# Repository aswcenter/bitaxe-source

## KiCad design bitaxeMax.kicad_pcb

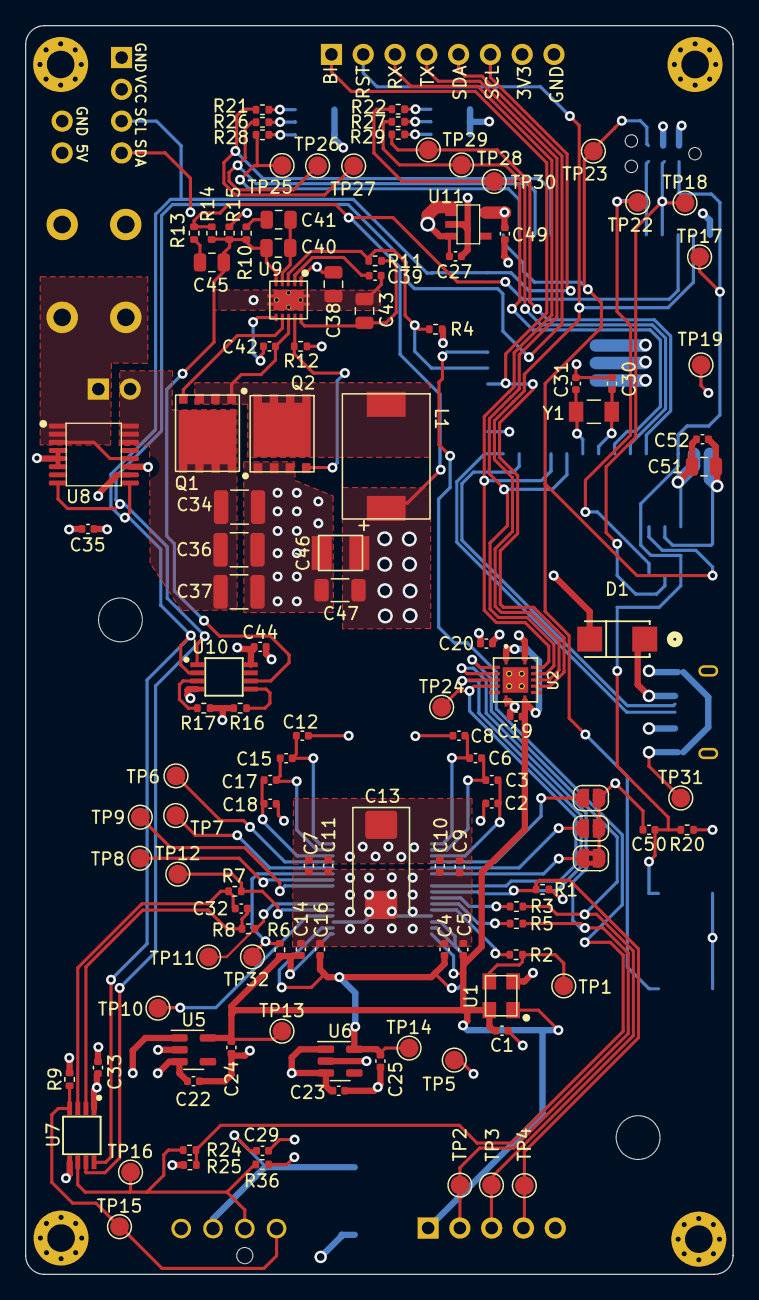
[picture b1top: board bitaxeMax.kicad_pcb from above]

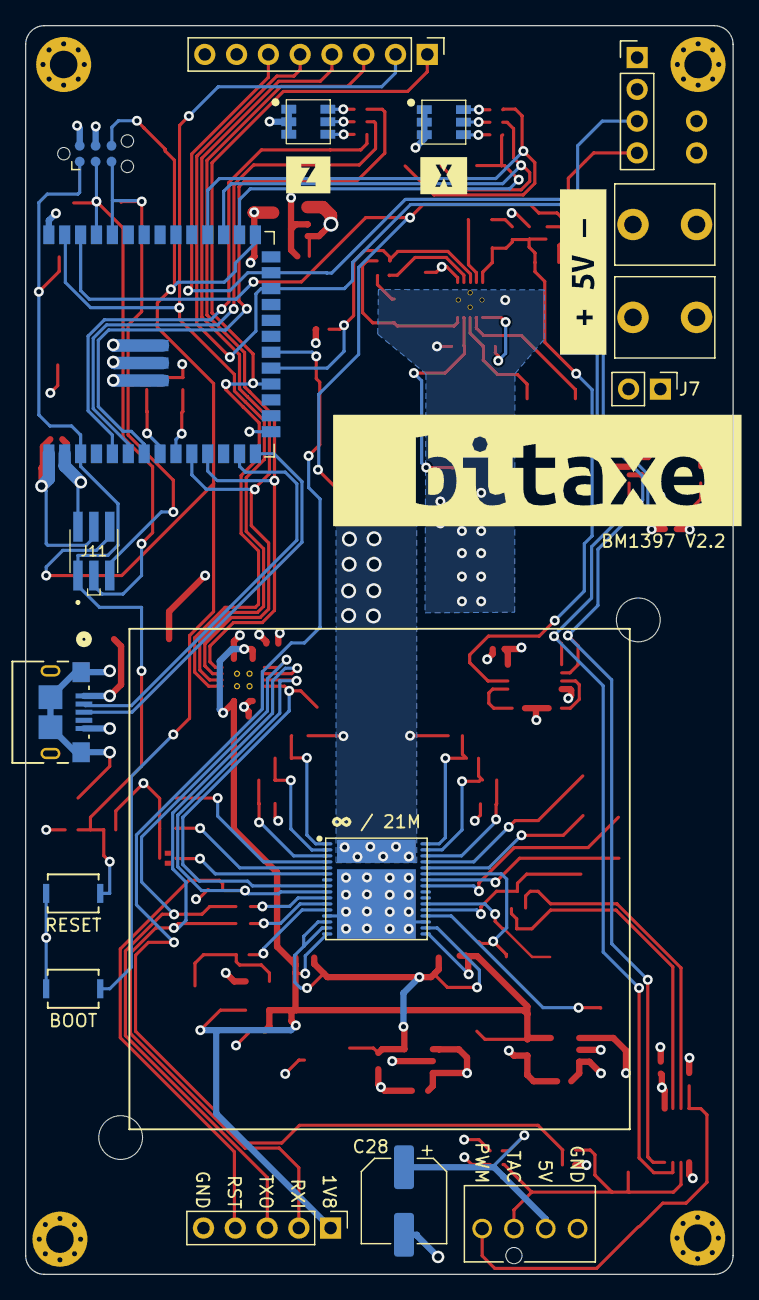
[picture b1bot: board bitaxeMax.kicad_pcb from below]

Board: 4 copper layers, 56.5 x 99.8 mm, 149 parts (21 on the bottom side), 77 nets.

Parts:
C1, C7, C9, C19, C20, C22, C23, C29, C33, C42, C52: 0.1uF; C_0402_1005Metric
C2, C3, C4, C5, C6, C8, C10, C11, C12, C14, C15, C16, C17, C18, C24, C25, C27, C35, C44, C49, C50: 1uF; C_0402_1005Metric
C13: 330uF; CP_EIA-7343-31_Kemet-D_Pad2.25x2.55mm_HandSolder
C28: 220uF; CP_Elec_6.3x7.7
C30, C31: 6.8pF; C_0402_1005Metric
C32: 470pF; C_0402_1005Metric
C34, C36, C37: 47uF; C_1210_3225Metric
C38: 1uF; C_0805_2012Metric
C39: 3.3nF; C_0402_1005Metric
C40: 180pF; C_0805_2012Metric
C41: 1.5nF; C_0805_2012Metric
C43, C51: 10uF; C_0805_2012Metric
C45: 470pF; C_0805_2012Metric
C46: 220uF; CAP_2R5TPE220MAFB
C47: 100uF; C_1206_3216Metric
D1: SS310; SMA_L4.3-W2.6-LS5.2-RD
H1, H2, H3, H4: AlignmentHole; MountingHole_2.2mm_M2_Pad_Via
H5, H6: MountingHole; MountingHole_3.5mm
IC1: BM1397_mode1; BM1397
J1, J2: Conn_01x01; 63862-1
J3: Conn_01x05; PinHeader_1x05_P2.54mm_Vertical
J4: Conn_01x04; 470531000
J5: TC2030-IDC; Tag-Connect_TC2030-IDC-NL_2x03_P1.27mm_Vertical
J6: Conn_01x08; PinHeader_1x08_P2.54mm_Vertical
J7: Conn_01x02; PinHeader_1x02_P2.54mm_Vertical
J9: Conn_01x04; PinHeader_1x04_P2.54mm_Vertical
J11: 20021121-00006C1LF; 2002112100006C1LF
JP1, JP2: SolderJumper_2_Open; SolderJumper-2_P1.3mm_Open_RoundedPad1.0x1.5mm
JP3: SolderJumper_2_Bridged; SolderJumper-2_P1.3mm_Bridged2Bar_RoundedPad1.0x1.5mm
L1: 150nH; FP1005R1-R15-R
Q1, Q2: CSD17311Q5
R1: 1k; R_0402_1005Metric
R2, R3, R5: 0; R_0402_1005Metric
R4, R6, R9, R20, R24, R36: 10k; R_0402_1005Metric
R7, R8, R26, R27: 100; R_0402_1005Metric
R10: 3.83k; R_0402_1005Metric
R11: 100k; R_0402_1005Metric
R12: 4.12k; R_0402_1005Metric
R13: 1.33k; R_0402_1005Metric
R14: 4.99k; R_0402_1005Metric
R15: 3.32k; R_0402_1005Metric
R16: 80k; R_0402_1005Metric
R17: DNP; R_0402_1005Metric
R21, R22: 60.4; R_0402_1005Metric
R25: 19.1k; R_0402_1005Metric
R28, R29: 261; R_0402_1005Metric
SW1, SW2: GT-TC029B-H025-L1N; SW_CS1213AGF260_CRS
TP1, TP2, TP3, TP4, TP5, TP6, TP7, TP8, TP9, TP10, TP11, TP12, TP13, TP14, TP15, TP16, TP17, TP18, TP19, TP22, TP23, TP24, TP25, TP26, TP27, TP28, TP29, TP30, TP31, TP32: TestPoint; TestPoint_Pad_D1.5mm
U1: 25MHz; O 25,0-JO32-B-1V3-1-T1-LF
U2: TXB0104RGYR; TXB0104
U4, U13: CLX6E-FKC; CLX6E-FKC-CH1M1D1BB7C3D3
U5: MCP1824T-1802E; SOT-23-5
U6: MCP1824T-0802E; SOT-23-5
U7: EMC2101; TSSOP-8_3x3mm_P0.65mm
U8: INA260; TSSOP-16_4.4x5mm_P0.65mm
U9: TPS40305
U10: DS4432U+; TSSOP-8_3x3mm_P0.65mm
U11: RT9080-33GJ5
U12: ESP32-S3-WROOM-1
USB1: 10118193-0001LF; USB_10118193-0001LF_AMP
Y1: 32.768kHz; SC32S-7PF20PPM
kibuzzard-63D74789: G***; kibuzzard-63D74789
kibuzzard-6387EEBE: G***; kibuzzard-6387EEBE
kibuzzard-6387EECB: G***; kibuzzard-6387EECB
kibuzzard-6392B1E5: G***; kibuzzard-6392B1E5

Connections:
/3V3: C20.1, C33.1, C35.1, C44.1, C49.1, C51.1, C52.1, J5.2, J6.7, J9.2, J11.2, R4.1, R9.2, R20.1, R36.2, TP19.1, U2.14 (VCCB), U7.1 (VDD), U8.10 (VS), U10.8 (VCC), U11.5 (VOUT), U12.2 (3V3), U12.15 (GPIO3/TOUCH3/ADC1_CH2*)
/5V: C22.1, C23.1, C27.1, C28.1, C29.1, C34.1, C36.1, C37.1, C38.1, D1.1, J4.2, J7.2, Q1.5 (D), U5.1 (VIN), U5.3 (EN), U6.1 (VIN), U6.3 (EN), U8.14 (IN-), U8.15 (IN-), U8.16 (IN-), U9.1 (VDD), U11.1 (VIN), U11.3 (EN)
/BI: J6.1, U2.10 (B4), U12.18 (GPIO10/TOUCH10/ADC1_CH9/FSPICS0/FSPIIO4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)
/BM1397/0V8: C4.1, C16.1, C25.1, IC1.14 (PLL_VDD), IC1.15 (VDDIO_08_0), IC1.18 (VDDIO_08_1), TP14.1, U6.5 (VOUT)
/BM1397/1V8: C1.2, C5.1, C14.1, C19.1, C24.1, IC1.16 (VDDIO_18_0), IC1.17 (VDDIO_18_1), J3.1, R6.2, TP13.1, U1.1 (EN), U1.4 (VIN), U2.1 (VCCA), U2.8 (OE), U5.5 (VOUT)
/BM1397/BM_BI: IC1.8 (BI), TP24.1, U2.5 (A4)
/BM1397/BM_CLKI: IC1.12 (CLKI), R2.2
/BM1397/CI: J3.2, R5.1, TP2.1, U2.3 (A2)
/BM1397/RO: J3.3, R3.1, TP3.1, U2.2 (A1)
/BM1397/RST_N: IC1.9 (NRSTI), J3.4, R1.2, TP4.1, U2.4 (A3)
/ESP32/EN: C50.1, J5.1, J11.1, R20.2, SW1.2, TP17.1, U12.3 (EN)
/ESP32/FAN_ALERT: R24.1, R25.2, U12.20 (GPIO12/TOUCH12/ADC2_CH1/FSPICLK/FSPIIO6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)
/ESP32/IO0: J5.6, J11.6, SW2.2, TP23.1, U12.27 (GPIO0/BOOT*)
/ESP32/LEDX_B: R21.1, TP27.1, U12.30 (SPIDQS/GPIO37/FSPIQ/SUBSPIQ)
/ESP32/LEDX_G: R26.1, TP26.1, U12.29 (SPIIO7/GPIO36/FSPICLK/SUBSPICLK)
/ESP32/LEDX_R: R28.1, TP25.1, U12.28 (SPIIO6/GPIO35/FSPID/SUBSPID)
/ESP32/LEDZ_B: R22.1, TP30.1, U12.7 (GPIO7/TOUCH7/ADC1_CH6)
/ESP32/LEDZ_G: R27.1, TP29.1, U12.6 (GPIO6/TOUCH6/ADC1_CH5)
/ESP32/LEDZ_R: R29.1, TP28.1, U12.5 (GPIO5/TOUCH5/ADC1_CH4)
/ESP32/P_RX: J5.5, J11.5, TP22.1, U12.36 (U0RXD/GPIO44/CLK_OUT2)
/ESP32/P_TX: J5.3, J11.3, TP18.1, U12.37 (U0TXD/GPIO43/CLK_OUT1)
/ESP32/XIN32: C30.1, U12.8 (GPIO15/U0RTS/ADC2_CH4/XTAL_32K_P), Y1.1
/ESP32/XOUT32: C31.1, U12.9 (GPIO16/U0CTS/ADC2_CH5/XTAL_32K_NH5), Y1.2
/Fan/FAN_PWM: J4.4, R9.1, TP15.1, U7.4 (FAN)
/Fan/FAN_TACH: J4.3, R24.2, R36.1, TP16.1, U7.6 (ALERT/TACH)
/Power/OUT0: C40.2, C45.2, R10.2, R14.2, R15.1, U9.5 (FB), U10.6 (OUT0)
/Power/PGOOD: R4.2, R11.1, U9.3 (PGOOD), U12.19 (GPIO11/TOUCH11/ADC2_CH0/FSPID/FSPIIO5/S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)
/Power/SW: C42.2, L1.1, Q1.1, Q1.2, Q1.3 (S), Q2.5 (D), U9.8 (SW)
/Power/VIN: J1.1, J7.1, U8.1 (IN+), U8.2 (IN+), U8.3 (IN+), U8.12 (VBUS)
/RST: J6.2, U2.11 (B3), U12.39 (GPIO1/TOUCH1/ADC1_CH0)
/RX: J6.3, U2.13 (B1), U12.11 (GPIO18/U1RXD/ADC2_CH7/CLK_OUT3)
/SCL: J6.6, J9.3, U7.8 (SMCLK), U8.9 (SCL), U10.2 (SCL), U12.25 (GPIO48/SPICLK_N/SUBSPICLK_N_DIFF)
/SDA: J6.5, J9.4, U7.7 (SMDATA), U8.8 (SDA), U10.1 (SDA), U12.24 (GPIO47/SPICLK_P/SUBSPICLK_P_DIFF)
/TEMP_N: IC1.21 (TEMP_N), R7.2, TP12.1
/TEMP_P: IC1.22 (TEMP_P), R8.1, TP11.1
/TX: J6.4, U2.12 (B2), U12.10 (GPIO17/U1TXD/ADC2_CH6)
/VDD: C7.1, C8.2, C9.1, C10.1, C11.1, C12.1, C13.1, C46.1, C47.1, IC1.33 (VDD), L1.2, R13.1, R14.1, U12.38 (GPIO2/TOUCH2/ADC1_CH1)
GND: C1.1, C2.1, C4.2, C5.2, C7.2, C9.2, C10.2, C11.2, C13.2, C14.2, C16.2, C18.2, C19.2, C20.2, C22.2, C23.2, C24.2, C25.2, C27.2, C28.2, C29.2, C30.2, C31.2, C33.2, C34.2, C35.2, C36.2, C37.2, C38.2, C39.2, C43.2, C44.2, C46.2, C47.2, C49.2, C50.2, C51.2, C52.2, IC1.13 (PLL_VSS), IC1.19 (VSS), IC1.34 (VSS_0), J2.1, J3.5, J4.1, J5.4, J6.8, J9.1, J11.4, JP1.1 (A), JP2.1 (A), JP3.1 (A), Q2.1, Q2.2, Q2.3 (S), R1.1, R12.2, R15.2, R16.2, R17.2, R25.1, SW1.1, SW2.1, TP5.1, TP31.1, U1.2 (GND), U2.7 (GND), U2.15 (GND), U2.16 (GND), U2.17 (GND), U2.18 (GND), U2.19 (GND), U4.1 (BC), U4.2 (GC), U4.3 (RC), U5.2 (GND), U6.2 (GND), U7.5 (GND), U8.4 (A1), U8.5 (A0), U8.6 (GND), U8.11 (GND), U9.11 (GND), U10.4 (GND), U11.2 (GND), U12.1 (GND), U12.40 (GND), U12.41 (GND), U13.1 (BC), U13.2 (GC), U13.3 (RC), USB1.5 (GND), USB1.6, USB1.7, USB1.8, USB1.9
unnamed: C41.2, R10.1
unnamed: C45.1, R13.2
unnamed: IC1.4 (ADDR0), JP1.2 (B)
unnamed: IC1.5 (ADDR1), JP2.2 (B)
unnamed: IC1.6 (ADDR2), JP3.2 (B)
unnamed: IC1.29 (BO), TP6.1
unnamed: IC1.11 (CI), R5.2
unnamed: IC1.25 (CLKO), TP9.1
unnamed: IC1.26 (CO), TP8.1
unnamed: IC1.28 (NRSTO), TP7.1
unnamed: IC1.20 (PIN_MODE), TP10.1
unnamed: IC1.27 (RI), R6.1, TP32.1
unnamed: IC1.10 (RO), R3.2
unnamed: C2.2, C3.1, IC1.3 (VDD1_0)
unnamed: C17.2, C18.1, IC1.30 (VDD1_1)
unnamed: C3.2, C6.1, IC1.2 (VDD2_0)
unnamed: C15.2, C17.1, IC1.31 (VDD2_1)
unnamed: C6.2, C8.1, IC1.1 (VDD3_0)
unnamed: C12.2, C15.1, IC1.32 (VDD3_1)
unnamed: Q1.4 (G), U9.7 (HDRV)
unnamed: Q2.4 (G), R12.1, U9.9 (LDRV)
unnamed: R2.1, TP1.1, U1.3 (OUT)
unnamed: R21.2, U4.6 (BA)
unnamed: R26.2, U4.5 (GA)
unnamed: R28.2, U4.4 (RA)
unnamed: C32.2, R7.1, U7.3 (DN)
unnamed: C32.1, R8.2, U7.2 (DP)
unnamed: C42.1, U9.6 (BOOT)
unnamed: C43.1, R11.2, U9.10 (BP)
unnamed: C40.1, C41.1, U9.4 (COMP)
unnamed: C39.1, U9.2 (SS)
unnamed: R16.1, U10.5 (FS0)
unnamed: R17.1, U10.3 (FS1)
unnamed: U12.13 (GPIO19/U1RTS/ADC2_CH8/CLK_OUT2/USB_D-), USB1.2 (D-)
unnamed: U12.14 (GPIO20/U1CTS/ADC2_CH9/CLK_OUT1/USB_D+), USB1.3 (D+)
unnamed: R22.2, U13.6 (BA)
unnamed: R27.2, U13.5 (GA)
unnamed: R29.2, U13.4 (RA)
unnamed: D1.2, USB1.1 (VBUS)

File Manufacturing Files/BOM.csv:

Id,Référence,Empreinte,Quantité,Désignation,Fournisseur et réf
1,"R26,R7,R27,R8",R_0402_1005Metric,4,100,
2,"C43,C51",C_0805_2012Metric,2,10uF,
3,"C19,C7,C1,C52,C33,C22,C42,C23,C29,C20,C9",C_0402_1005Metric,11,0.1uF,
4,U8,TSSOP-16_4.4x5mm_P0.65mm,1,INA260,
5,D1,SMA_L4.3-W2.6-LS5.2-RD,1,SS310,
6,R13,R_0402_1005Metric,1,1.33k,
7,C41,C_0805_2012Metric,1,1.5nF,
8,"C3,C25,C50,C4,C12,C15,C16,C49,C18,C35,C10,C11,C14,C44,C6,C2,C5,C17,C8,C27,C24",C_0402_1005Metric,21,1uF,
9,C38,C_0805_2012Metric,1,1uF,
10,C45,C_0805_2012Metric,1,470pF,
11,Y1,SC32S-7PF20PPM,1,32.768kHz,
12,U5,SOT-23-5,1,MCP1824T-1802E,
13,"R6,R36,R20,R4,R24,R9",R_0402_1005Metric,6,10k,
14,U6,SOT-23-5,1,MCP1824T-0802E,
15,U7,TSSOP-8_3x3mm_P0.65mm,1,EMC2101,
16,"R29,R28",R_0402_1005Metric,2,261,
17,"C30,C31",C_0402_1005Metric,2,6.8pF,
18,",",,2,,
19,U2,TXB0104,1,TXB0104RGYR,
20,R10,R_0402_1005Metric,1,3.83k,
21,L1,FP1005R1-R15-R,1,150nH,
22,R15,R_0402_1005Metric,1,3.32k,
23,R16,R_0402_1005Metric,1,80k,
24,C32,C_0402_1005Metric,1,470pF,
25,"R3,R2,R5",R_0402_1005Metric,3,0,
26,C40,C_0805_2012Metric,1,180pF,
27,U10,TSSOP-8_3x3mm_P0.65mm,1,DS4432U+,
28,C39,C_0402_1005Metric,1,3.3nF,
29,R14,R_0402_1005Metric,1,4.99k,
30,R11,R_0402_1005Metric,1,100k,
31,C13,CP_EIA-7343-31_Kemet-D_Pad2.25x2.55mm_HandSolder,1,330uF,
32,"Q2,Q1",CSD17311Q5,2,CSD17311Q5,
33,U9,TPS40305,1,TPS40305,
34,C46,CAP_2R5TPE220MAFB,1,220uF,
35,R25,R_0402_1005Metric,1,19.1k,
36,R17,R_0402_1005Metric,1,DNP,
37,"C34,C36,C37",C_1210_3225Metric,3,47uF,
38,U1,"O 25,0-JO32-B-1V3-1-T1-LF",1,25MHz,
39,R12,R_0402_1005Metric,1,4.12k,
40,"R22,R21",R_0402_1005Metric,2,"60,4",
41,C47,C_1206_3216Metric,1,100uF,
42,U11,RT9080-33GJ5,1,RT9080-33GJ5,
43,"SW1,SW2",SW_CS1213AGF260_CRS,2,GT-TC029B-H025-L1N,
44,J4,470531000,1,Conn_01x04,
45,"J2,J1",63862-1,2,Conn_01x01,
46,J7,PinHeader_1x02_P2.54mm_Vertical,1,Conn_01x02,
47,J3,PinHeader_1x05_P2.54mm_Vertical,1,Conn_01x05,
48,U12,ESP32-S3-WROOM-1,1,ESP32-S3-WROOM-1,
49,IC1,BM1397,1,BM1397_mode1,
50,"U13,U4",CLX6E-FKC-CH1M1D1BB7C3D3,2,CLX6E-FKC,
51,C28,CP_Elec_6.3x7.7,1,220uF,
52,J11,2002112100006C1LF,1,20021121-00006C1LF,
53,USB1,USB_10118193-0001LF_AMP,1,10118193-0001LF,
